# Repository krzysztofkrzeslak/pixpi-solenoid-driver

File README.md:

# pixpi-sound-sensor
Repository which holds solenoid driver sources(schematic and board)for PiXPi controller <br/>

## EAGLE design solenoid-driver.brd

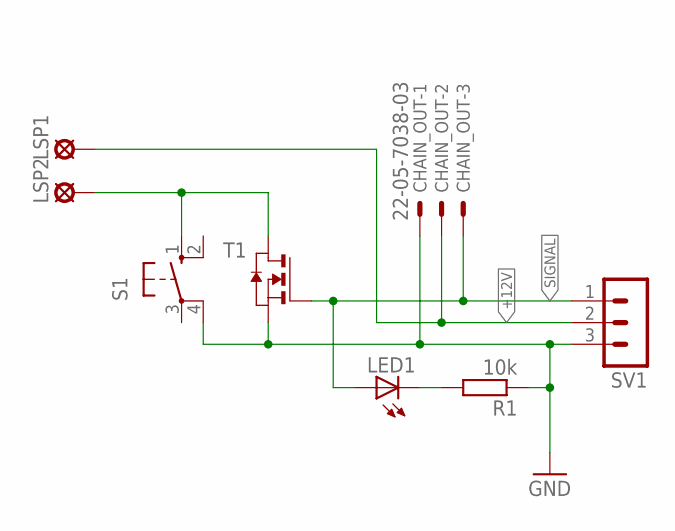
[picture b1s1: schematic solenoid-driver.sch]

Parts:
CHAIN_OUT: 22-05-7038-03; 7395-03
LED1: LEDCHIPLED_1206; CHIPLED_1206
LSP1, LSP2: LSP13
R1: 10k; M0805
S1: 10-XX; B3F-10XX
SV1: MA03-1
T1: NMOSSOT23; SOT-23

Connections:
+12V: CHAIN_OUT.2, LSP1.MP, SV1.2
GND: CHAIN_OUT.1, R1.1, S1.4 (P1), SV1.3, T1.2 (S)
unnamed: LSP2.MP, S1.1 (S), T1.1 (D)
unnamed: LED1.C, R1.2
SIGNAL: CHAIN_OUT.3, LED1.A, SV1.1, T1.3 (G)

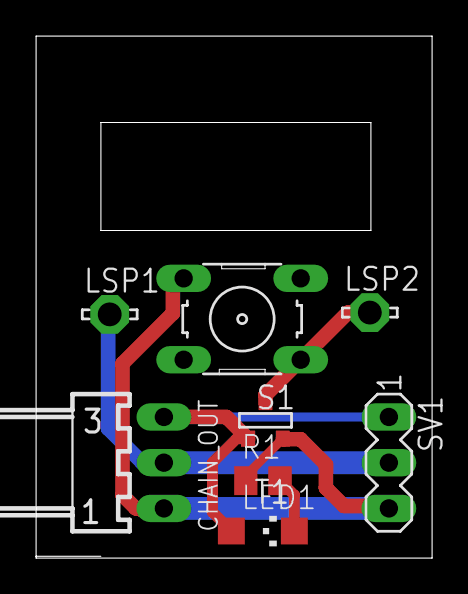
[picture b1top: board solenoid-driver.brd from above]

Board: 2 copper layers, 22.0 x 29.0 mm, 8 parts (0 on the bottom side), 5 nets.

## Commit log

2019-08-23 Added schematic, board and readme
